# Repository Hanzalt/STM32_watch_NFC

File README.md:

# HolTyc Smartwatch

A smartwatch designed and engineered from scratch by Czech students. This is a hobby project intended to help others build their own PCB-based watches.

| Front | Back |
|:-----:|:----:|
|  |  |

---

## Features

- **Analog clock** — 12 addressable RGB LEDs (WS2812B) arranged in a clock ring
- **Digital clock** — HH:MM shown on a custom 7-segment display built using **Charlieplexing** (6 GPIO pins drive a 4-digit matrix with no external drivers)
- **Wrist-wake** — BMA400 accelerometer detects wrist raise, wakes the watch from sleep
- **Auto-brightness** — BH1750FVI ambient light sensor adjusts LED brightness automatically
- **6 color themes** — cycle through hour/minute color combinations
- **Time setting** — set time directly on the watch via buttons
- **Shooting mini-game** — hidden game accessible via simultaneous button press
- **Battery monitoring** — color-coded charging display
- **Ultra-low power** — STM32 STOP mode between interactions; RTC runs from LSE crystal

---

## Repository Structure

```
STM32_watch_NFC/
├── Firmware/               # STM32CubeIDE project (all firmware source code)
│   └── Core/
│       ├── Inc/            # Header files (main.h, BMA400.h, Din_LED.h, …)
│       └── Src/            # Source files (main.c, BMA400.c, Din_LED.c, …)
├── PCB/                    # KiCad project — schematic and PCB layout
│   └── STM32_watch_NFC/    # Main KiCad project files (.kicad_pcb, .kicad_sch, gerbers)
├── Firmware_old/           # Legacy firmware from earlier revisions (deprecated)
├── Datasheets_components/  # Datasheets for key ICs (STM32, BMA400, TPS63802, …)
├── HW_design/              # Hardware design notes and segment layout diagrams
├── Fotos/                  # PCB renders and design visuals
└── README.md
```

---

## Hardware

| Component | Part | Notes |
|-----------|------|-------|
| MCU | STM32L031G6U6 | Cortex-M0+, 32KB Flash, 8KB RAM |
| RGB LEDs | 12× WS2812B | Driven via TIM2 PWM + DMA |
| Display | Charlieplex matrix | 6 pins → 4-digit 7-segment (no external drivers) |
| Accelerometer | BMA400 | Wrist-wake via orientation interrupt |
| Light sensor | BH1750FVI | Auto-brightness (I2C) |
| Power converter | TPS63802 | Buck-boost regulator |
| RTC crystal | 32.768 kHz LSE | Accurate timekeeping in sleep |
| Buzzer | Passive | ~2.7 kHz tone |

The HH:MM display is built entirely with Charlieplexing — 6 GPIO pins control a 4-digit 7-segment matrix with no shift registers or external display drivers.

### Power Schematic

> **Note:** The PCB had NFC hardware (ST25R3916B antenna area), but NFC functionality was scrapped during development. No NFC code exists in the firmware.

---

## Getting Started

### Requirements

- [STM32CubeIDE](https://www.st.com/en/development-tools/stm32cubeide.html) (recommended: 1.14+)
- ST-Link programmer (or compatible SWD debugger)
- The watch hardware (or a compatible STM32L031 dev board for partial testing)

### Import & Build

1. Open STM32CubeIDE.
2. Go to **File → Import → General → Existing Projects into Workspace**.
3. Set the root directory to `Firmware/` and select the project.
4. Click **Finish**.
5. Build with **Project → Build Project** (or `Ctrl+B`).

### Flash

1. Connect your ST-Link to the watch via the SWD pads on the PCB.
2. In STM32CubeIDE, go to **Run → Debug Configurations** and select the ST-Link configuration.
3. Click **Debug** (or **Run**) to flash and start.

Alternatively, flash the compiled `.elf` / `.bin` from `Firmware/Debug/` using **STM32CubeProgrammer**.

### First Boot

- The RTC starts paused at 00:00:00. Set the time via **Button_R long-press** → enter `changeTime` mode.
- Time resets on power loss (no backup registers).

---

## Button Reference

| Button | Short press | Long press (≥1 s) |
|--------|-------------|-------------------|
| Button_R | Show RGB analog clock | Enter time-set mode |
| Button_LT | Show digital clock | Enter charging display |
| Button_LB | Show digital clock | Cycle color theme |
| Button_R + Button_LB | Enter shooting game | — |

---

## PCB

KiCad source files are in `PCB/STM32_watch_NFC/`. Gerber files ready for manufacturing are in `PCB/STM32_watch_NFC/gerber/`. A panelized version is available in `PCB/Panelized_watch/`.

---

## License

MIT License

Copyright (c) 2025 HolTyc

Permission is hereby granted, free of charge, to any person obtaining a copy of this software and associated documentation files (the "Software"), to deal in the Software without restriction, including without limitation the rights to use, copy, modify, merge, publish, distribute, sublicense, and/or sell copies of the Software, and to permit persons to whom the Software is furnished to do so, subject to the following conditions:

The above copyright notice and this permission notice shall be included in all copies or substantial portions of the Software.

THE SOFTWARE IS PROVIDED "AS IS", WITHOUT WARRANTY OF ANY KIND, EXPRESS OR IMPLIED, INCLUDING BUT NOT LIMITED TO THE WARRANTIES OF MERCHANTABILITY, FITNESS FOR A PARTICULAR PURPOSE AND NONINFRINGEMENT. IN NO EVENT SHALL THE AUTHORS OR COPYRIGHT HOLDERS BE LIABLE FOR ANY CLAIM, DAMAGES OR OTHER LIABILITY, WHETHER IN AN ACTION OF CONTRACT, TORT OR OTHERWISE, ARISING FROM, OUT OF OR IN CONNECTION WITH THE SOFTWARE OR THE USE OR OTHER DEALINGS IN THE SOFTWARE.

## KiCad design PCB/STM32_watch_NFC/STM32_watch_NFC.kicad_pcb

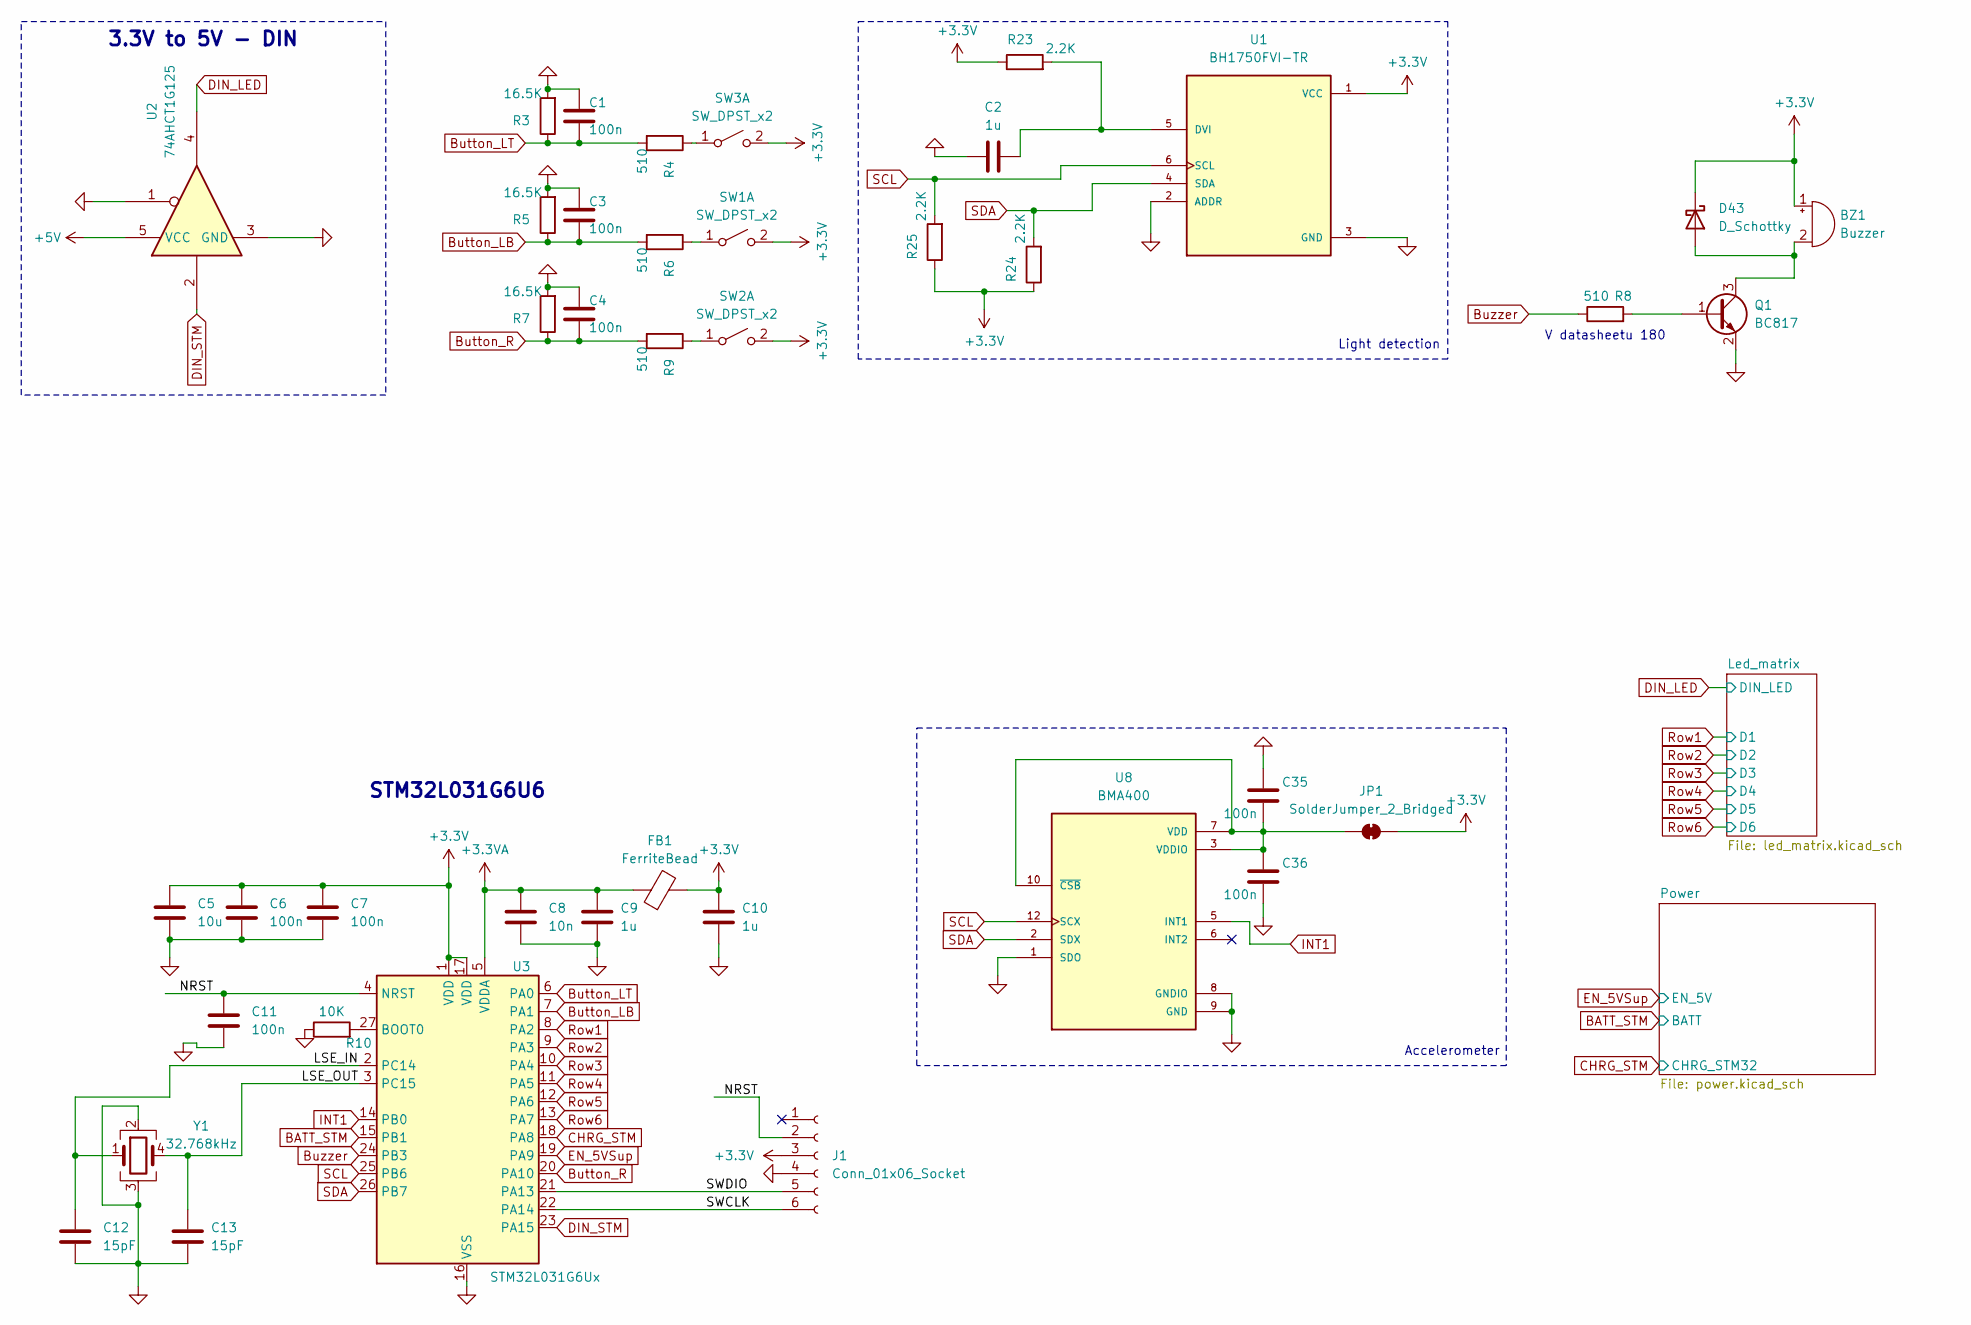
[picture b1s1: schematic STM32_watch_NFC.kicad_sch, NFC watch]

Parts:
BZ1: Buzzer; Buzzer_SMD; LCSC C95299
C1, C3, C4, C6, C7, C11, C35, C36: 100n; C_0201_0603Metric; LCSC C7393837
C2, C9, C10: 1u; C_0402_1005Metric; LCSC C52923
C5: 10u; C_0603_1608Metric; LCSC C19702
C8: 10n; C_0402_1005Metric; LCSC C15195
C12, C13: 15pF; C_0402_1005Metric; LCSC C1548
D43: D_Schottky; D_SOD-523; LCSC C727120
FB1: FerriteBead; L_0603_1608Metric; LCSC C1002
J1: Conn_01x06_Socket; JST_SUR_SM06B-SURS-TF_1x06-1MP_P0.80mm_Horizontal; LCSC C495545
JP1: SolderJumper_2_Bridged; SolderJumper-2_P1.3mm_Bridged_RoundedPad1.0x1.5mm
Q1: BC817; SOT-23; LCSC C52801
R3, R5, R7: 16.5K; R_0805_2012Metric; LCSC C104028
R4, R6, R8, R9: 510; R_0402_1005Metric; LCSC C25123
R10: 10K; R_0402_1005Metric; LCSC C25744
R23, R24, R25: 2.2K; R_0402_1005Metric; LCSC C25879
SW1, SW2, SW3: SW_DPST_x2; Panasonic_EVQPUJ_EVQPUA; LCSC C128539
U1: BH1750FVI-TR; XDCR_BH1750FVI-TR; LCSC C78960
U2: 74AHCT1G125; SOT-353_SC-70-5; LCSC C350557
U3: STM32L031G6Ux; QFN-28_4x4mm_P0.5mm; LCSC C96514
U8: BMA400; XDCR_BMA400
Y1: 32.768kHz; Crystal_SMD_SeikoEpson_MC146-4Pin_6.7x1.5mm; LCSC C7466130

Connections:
+3.3V: BZ1.1 (+), C5.1, C6.1, C7.1, C10.2, D43.1 (K), FB1.2, J1.3, JP1.2 (B), R23.1, R24.1, R25.1, SW1.2 (B), SW2.2 (B), SW3.2 (B), U1.1 (VCC), U3.1 (VDD), U3.17 (VDD); also elsewhere on the board
+3.3VA: C8.1, C9.2, FB1.1, U3.5 (VDDA)
+5V: U2.5 (VCC); also elsewhere on the board
/LSE_IN: C12.1, U3.2 (PC14), Y1.1
/LSE_OUT: C13.1, U3.3 (PC15), Y1.4
/NRST: C11.1, J1.2, U3.4 (NRST)
/SWCLK: J1.6, U3.22 (PA14)
/SWDIO: J1.5, U3.21 (PA13)
BATT_STM: U3.15 (PB1); also elsewhere on the board
Button_LB: C3.2, R5.1, R6.2, U3.7 (PA1)
Button_LT: C1.2, R3.1, R4.2, U3.6 (PA0)
Button_R: C4.2, R7.1, R9.2, U3.20 (PA10)
Buzzer: R8.1, U3.24 (PB3)
CHRG_STM: U3.18 (PA8); also elsewhere on the board
DIN_LED: U2.4; also elsewhere on the board
DIN_STM: U2.2, U3.23 (PA15)
EN_5VSup: U3.19 (PA9); also elsewhere on the board
GND: C1.1, C2.2, C3.1, C4.1, C5.2, C6.2, C7.2, C8.2, C9.1, C10.1, C11.2, C12.2, C13.2, C35.1, C36.2, J1.4, Q1.2 (E), R3.2, R5.2, R7.2, R10.1, U1.2 (ADDR), U1.3 (GND), U2.1, U2.3 (GND), U3.16 (VSS), U3.28 (VSS), U8.1 (SDO), U8.8 (GNDIO), U8.9 (GND), Y1.2, Y1.3; also elsewhere on the board
INT1: U3.14 (PB0), U8.5 (INT1)
unnamed: BZ1.2 (-), D43.2 (A), Q1.3 (C)
unnamed: C35.2, C36.1, JP1.1 (A), U8.3 (VDDIO), U8.7 (VDD), U8.10 (~CSB)
unnamed: Q1.1 (B), R8.2
unnamed: R6.1, SW1.1 (A)
unnamed: R9.1, SW2.1 (A)
unnamed: R4.1, SW3.1 (A)
unnamed: C2.1, R23.2, U1.5 (DVI)
unnamed: R10.2, U3.27 (BOOT0)
Row1: U3.8 (PA2); also elsewhere on the board
Row2: U3.9 (PA3); also elsewhere on the board
Row3: U3.10 (PA4); also elsewhere on the board
Row4: U3.11 (PA5); also elsewhere on the board
Row5: U3.12 (PA6); also elsewhere on the board
Row6: U3.13 (PA7); also elsewhere on the board
SCL: R25.2, U1.6 (SCL), U3.25 (PB6), U8.12 (SCX)
SDA: R24.2, U1.4 (SDA), U3.26 (PB7), U8.2 (SDX)

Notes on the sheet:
Light detection
V datasheetu 180
Accelerometer
3.3V to 5V - DIN
STM32L031G6U6

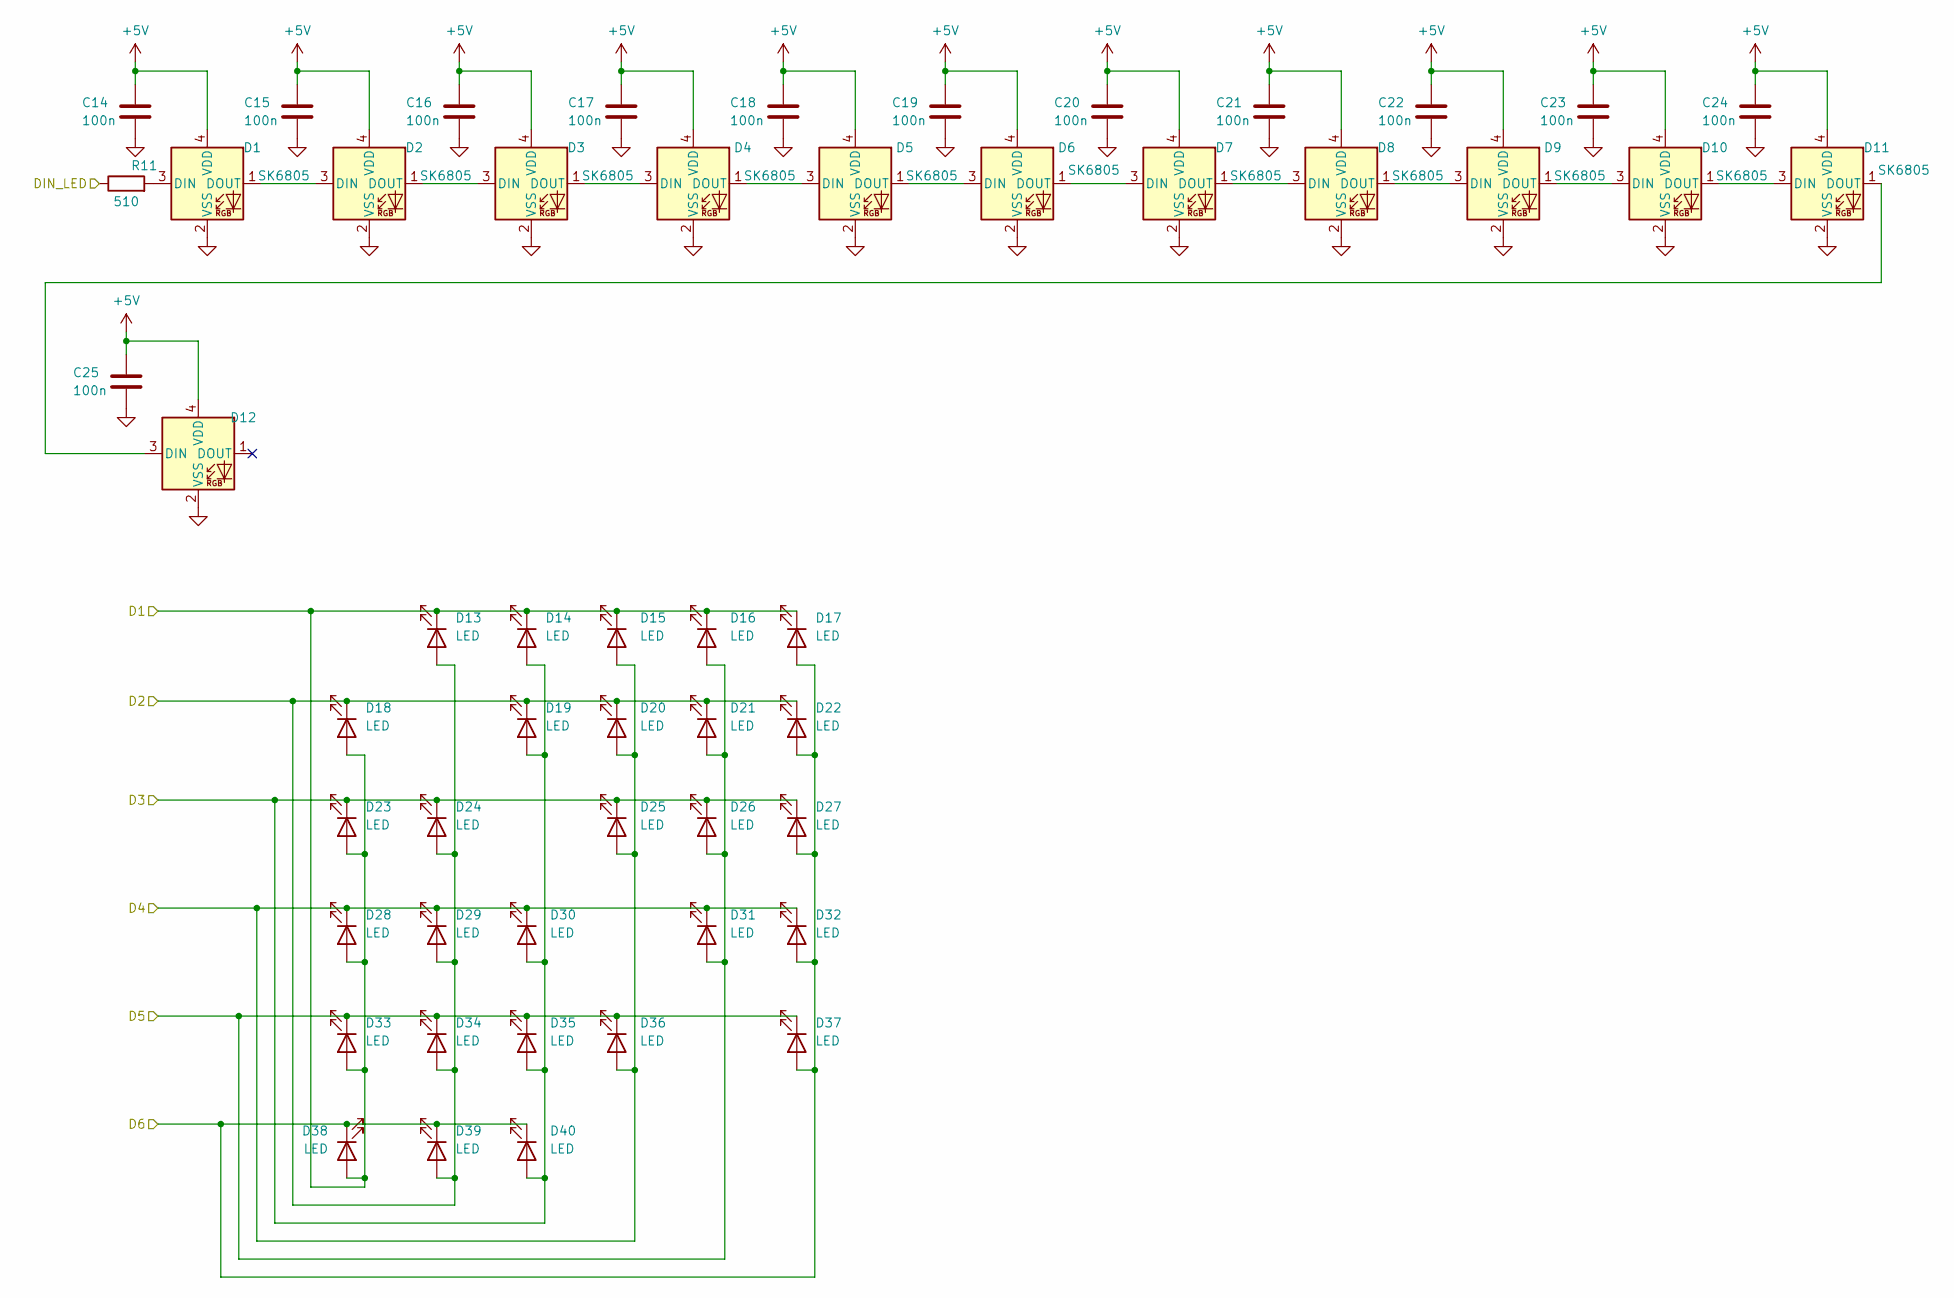
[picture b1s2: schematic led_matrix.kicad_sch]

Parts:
C14, C15, C16, C17, C18, C19, C20, C21, C22, C23, C24, C25: 100n; C_0201_0603Metric; LCSC C7393837
D1, D2, D3, D4, D5, D6, D7, D8, D9, D10, D11, D12: SK6805; LED_SK6812_EC15_1.5x1.5mm; LCSC C2890035
D13, D14, D15, D16, D17, D18, D19, D20, D21, D22, D23, D24, D25, D26, D27, D28, D29, D30, D31, D32, D33, D34, D35, D36, D37, D38, D39, D40: LED; LED_0402_1005Metric; LCSC C20613596
R11: 510; R_0402_1005Metric; LCSC C25123

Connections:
+5V: C14.1, C15.1, C16.1, C17.1, C18.1, C19.1, C20.1, C21.1, C22.1, C23.1, C24.1, C25.1, D1.4 (VDD), D2.4 (VDD), D3.4 (VDD), D4.4 (VDD), D5.4 (VDD), D6.4 (VDD), D7.4 (VDD), D8.4 (VDD), D9.4 (VDD), D10.4 (VDD), D11.4 (VDD), D12.4 (VDD); also elsewhere on the board
DIN_LED: R11.1; also elsewhere on the board
GND: C14.2, C15.2, C16.2, C17.2, C18.2, C19.2, C20.2, C21.2, C22.2, C23.2, C24.2, C25.2, D1.2 (VSS), D2.2 (VSS), D3.2 (VSS), D4.2 (VSS), D5.2 (VSS), D6.2 (VSS), D7.2 (VSS), D8.2 (VSS), D9.2 (VSS), D10.2 (VSS), D11.2 (VSS), D12.2 (VSS); also elsewhere on the board
unnamed: D1.3 (DIN), R11.2
unnamed: D1.1 (DOUT), D2.3 (DIN)
unnamed: D2.1 (DOUT), D3.3 (DIN)
unnamed: D3.1 (DOUT), D4.3 (DIN)
unnamed: D4.1 (DOUT), D5.3 (DIN)
unnamed: D5.1 (DOUT), D6.3 (DIN)
unnamed: D6.1 (DOUT), D7.3 (DIN)
unnamed: D7.1 (DOUT), D8.3 (DIN)
unnamed: D8.1 (DOUT), D9.3 (DIN)
unnamed: D9.1 (DOUT), D10.3 (DIN)
unnamed: D10.1 (DOUT), D11.3 (DIN)
unnamed: D11.1 (DOUT), D12.3 (DIN)
Row1: D13.1 (K), D14.1 (K), D15.1 (K), D16.1 (K), D17.1 (K), D18.2 (A), D23.2 (A), D28.2 (A), D33.2 (A), D38.2 (A); also elsewhere on the board
Row2: D13.2 (A), D18.1 (K), D19.1 (K), D20.1 (K), D21.1 (K), D22.1 (K), D24.2 (A), D29.2 (A), D34.2 (A), D39.2 (A); also elsewhere on the board
Row3: D14.2 (A), D19.2 (A), D23.1 (K), D24.1 (K), D25.1 (K), D26.1 (K), D27.1 (K), D30.2 (A), D35.2 (A), D40.2 (A); also elsewhere on the board
Row4: D15.2 (A), D20.2 (A), D25.2 (A), D28.1 (K), D29.1 (K), D30.1 (K), D31.1 (K), D32.1 (K), D36.2 (A); also elsewhere on the board
Row5: D16.2 (A), D21.2 (A), D26.2 (A), D31.2 (A), D33.1 (K), D34.1 (K), D35.1 (K), D36.1 (K), D37.1 (K); also elsewhere on the board
Row6: D17.2 (A), D22.2 (A), D27.2 (A), D32.2 (A), D37.2 (A), D38.1 (K), D39.1 (K), D40.1 (K); also elsewhere on the board

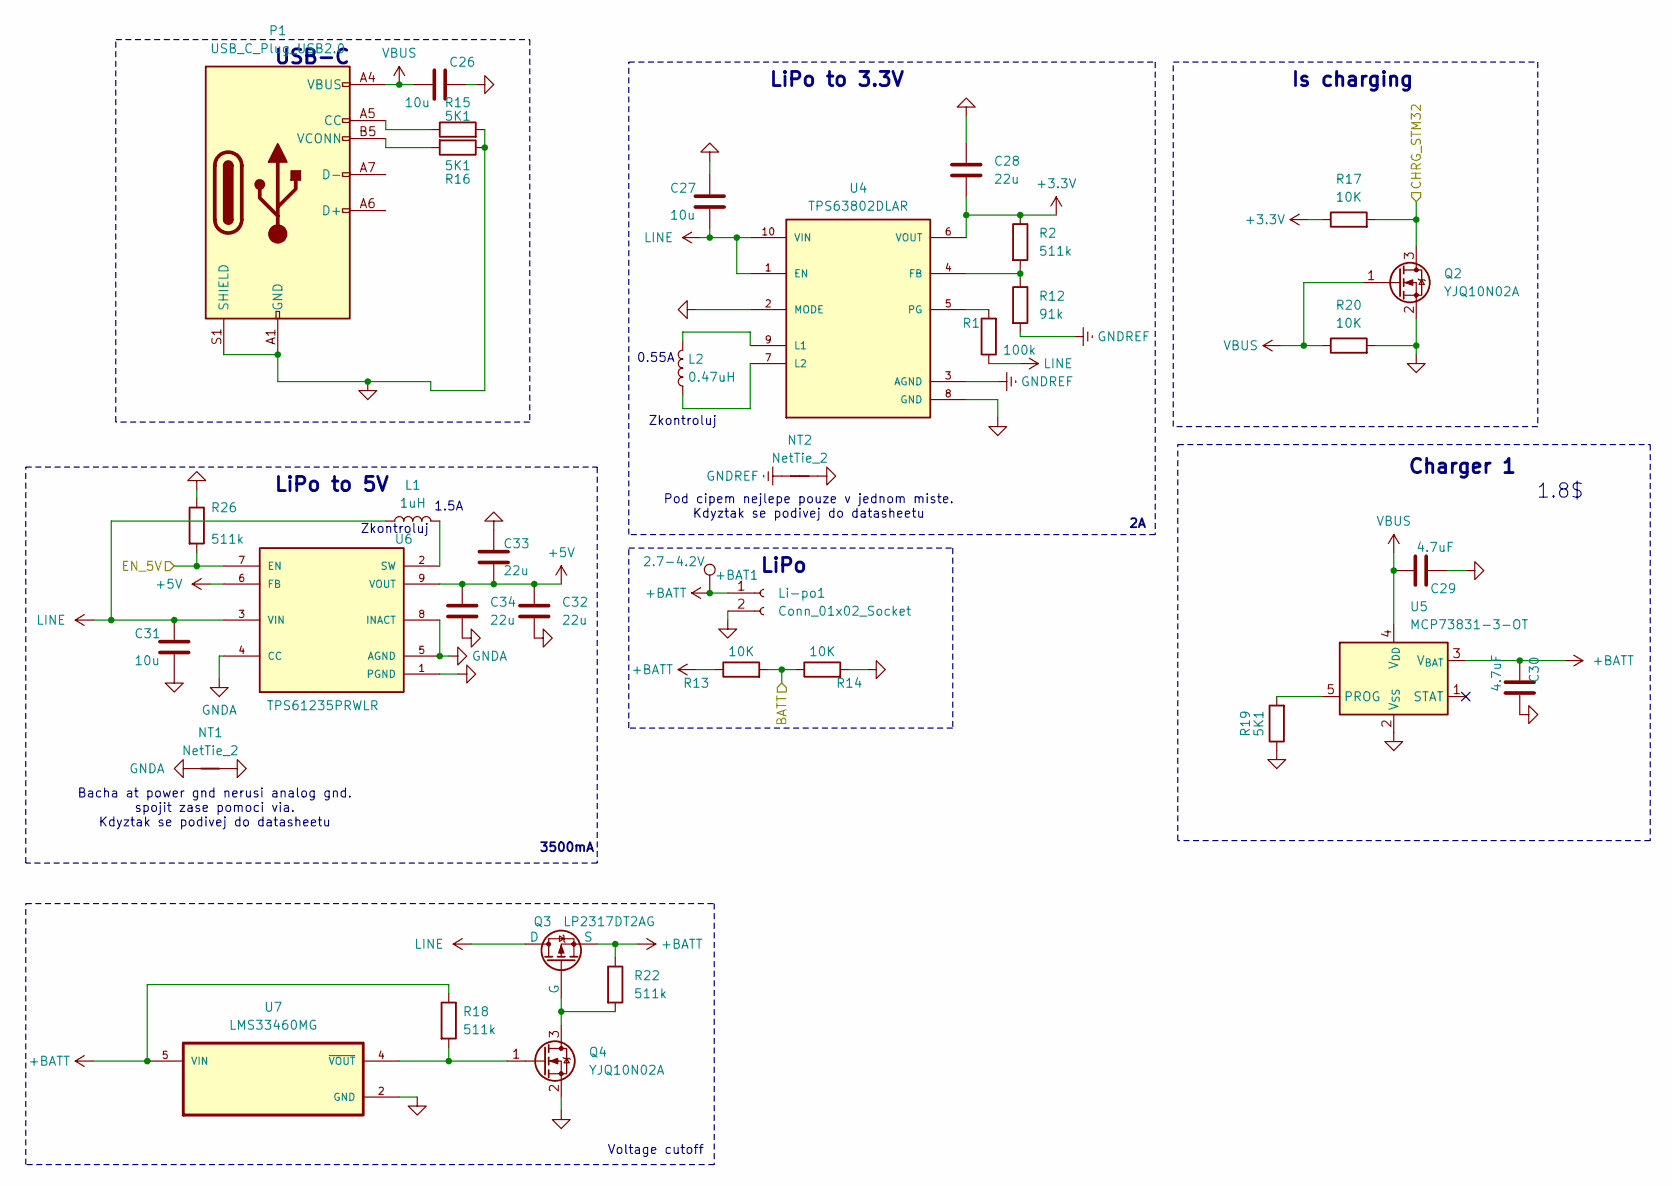
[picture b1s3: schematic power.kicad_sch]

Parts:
+BAT1: 2.7-4.2V; TestPoint_Pad_D1.5mm
C26, C27, C31: 10u; C_0603_1608Metric; LCSC C19702
C28, C32, C33, C34: 22u; C_0603_1608Metric; LCSC C59461
C29, C30: 4.7uF; C_0603_1608Metric; LCSC C19666
L1: 1uH; L_1008_2520Metric; LCSC C76795
L2: 0.47uH; L_0805_2012Metric; LCSC C370012
Li-po1: Conn_01x02_Socket; Molex_Pico-EZmate_78171-0002_1x02-1MP_P1.20mm_Vertical; LCSC C505023
NT1, NT2: NetTie_2; NetTie-2_SMD_Pad0.5mm
P1: USB_C_Plug_USB2.0; USB_C_Receptacle_GCT_USB4135-GF-A_6P_TopMnt_Horizontal; LCSC C2681548
Q2, Q4: YJQ10N02A; Diodes_UDFN2020-6_Type-F; LCSCv C919558
Q3: LP2317DT2AG; Diodes_UDFN2020-6_Type-F; LCSC C383254
R1: 100k; R_0603_1608Metric; LCSC C25803
R2, R18, R22, R26: 511k; R_0603_1608Metric; LCSC C2930114
R12: 91k; R_0603_1608Metric; LCSC C2907077
R13, R14, R17, R20: 10K; R_0402_1005Metric; LCSC C25744
R15, R16, R19: 5K1; R_0402_1005Metric; LCSC C25905
U4: TPS63802DLAR; VREG_TPS63802DLAR; LCSC C2845237
U5: MCP73831-3-OT; SOT-23-5; LCSC C625598
U6: TPS61235PRWLR; CONV_TPS61235PRWLR
U7: LMS33460MG; SOT65P210X110-5N; LCSC C95686

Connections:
+3.3V: C28.2, R2.1, R17.1, U4.6 (VOUT); also elsewhere on the board
+5V: C32.1, C33.2, C34.1, U6.6 (FB), U6.9 (VOUT); also elsewhere on the board
+BATT: +BAT1.1, C30.2, Li-po1.1, Q3.3 (S), R13.1, R18.1, R22.1, U5.3 (V_{BAT}), U7.5 (VIN)
/Power/DONE: U5.1 (STAT); also elsewhere on the board
BATT_STM: R13.2, R14.1; also elsewhere on the board
CHRG_STM: Q2.3 (D), R17.2; also elsewhere on the board
EN_5VSup: R26.2, U6.7 (EN); also elsewhere on the board
GND: C26.2, C27.1, C28.1, C29.2, C30.1, C31.2, C32.2, C33.1, C34.2, Li-po1.2, NT1.2, NT2.2, P1.A1 (GND), P1.A12 (GND), P1.B1 (GND), P1.B12 (GND), P1.S1 (SHIELD), Q2.2 (S), Q4.2 (S), R14.2, R15.2, R16.1, R19.1, R20.2, R26.1, U4.2 (MODE), U4.8 (GND), U5.2 (V_{SS}), U6.1 (PGND), U7.2 (GND), U7.3 (GND); also elsewhere on the board
GNDA: NT1.1, U6.4 (CC), U6.5 (AGND), U6.8 (INACT)
GNDREF: NT2.1, R12.2, U4.3 (AGND)
LINE: C27.2, C31.1, L1.1, Q3.1 (D), R1.1, U4.1 (EN), U4.10 (VIN), U6.3 (VIN)
unnamed: P1.A5 (CC), R15.1
unnamed: P1.B5 (VCONN), R16.2
unnamed: Q3.2 (G), Q4.3 (D), R22.2
unnamed: Q4.1 (G), R18.2, U7.4 (~VOUT)
unnamed: R2.2, R12.1, U4.4 (FB)
unnamed: L2.2, U4.9 (L1)
unnamed: L2.1, U4.7 (L2)
unnamed: R1.2, U4.5 (PG)
unnamed: R19.2, U5.5 (PROG)
unnamed: L1.2, U6.2 (SW)
VBUS: C26.1, C29.1, P1.A4 (VBUS), P1.A9 (VBUS), P1.B4 (VBUS), P1.B9 (VBUS), Q2.1 (G), R20.1, U5.4 (V_{DD}); also elsewhere on the board

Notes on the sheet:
Zkontroluj
Voltage cutoff
1.8$
LiPo to 3.3V
Bacha at power gnd nerusi analog gnd. spojit zase pomoci via. Kdyztak se podivej do datasheetu
Is charging
USB-C
3500mA
LiPo to 5V
0.55A
1.5A
LiPo
Charger 1
Pod cipem nejlepe pouze v jednom miste. Kdyztak se podivej do datasheetu

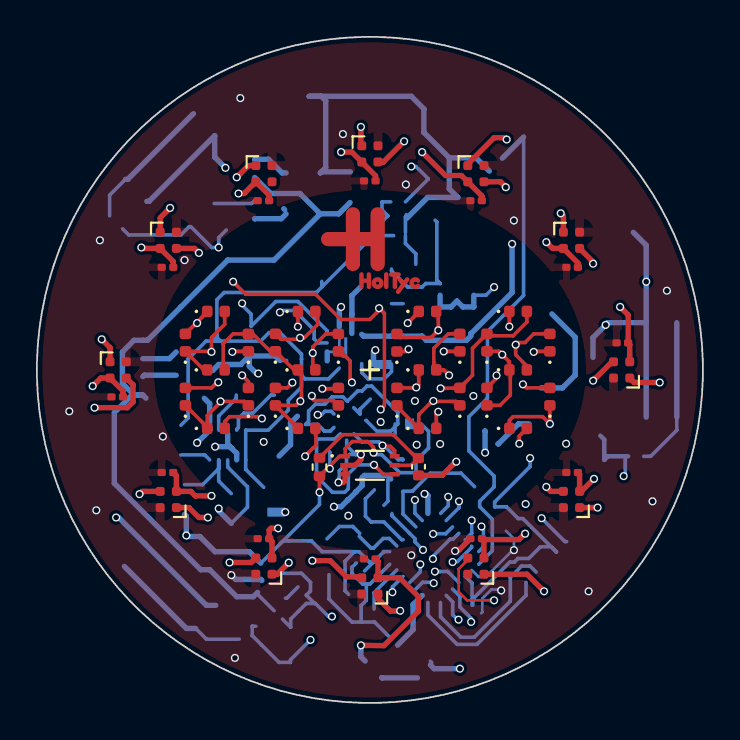
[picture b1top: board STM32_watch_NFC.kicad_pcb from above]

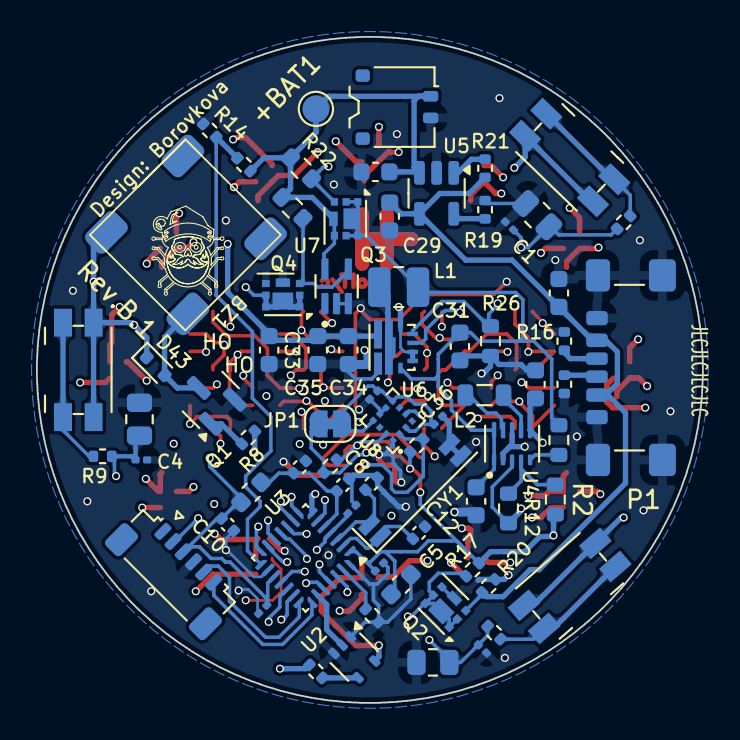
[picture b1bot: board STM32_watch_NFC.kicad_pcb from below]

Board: 4 copper layers, 37.0 x 37.0 mm, 130 parts (75 on the bottom side), 63 nets.

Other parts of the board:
R21: 10k; R_0402_1005Metric

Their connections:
/Power/DONE: R21.1; also elsewhere on the board
VBUS: R21.2; also elsewhere on the board

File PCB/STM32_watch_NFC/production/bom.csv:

Designator,Footprint,Quantity,Value,LCSC Part #
BZ1,Buzzer_SMD,1,Buzzer,C95299
"C1, C11, C14, C15, C16, C17, C18, C19, C20, C21, C22, C23, C24, C25, C3, C4, C6, C7",0201,18,100n,C7393837
"C10, C2, C27, C28, C9",0402,5,1u,C52923
"C12, C13",0402,2,15pF,C1548
"C26, C31, C32, C5",0603,4,10u,C19702
"C29, C30",0603,2,4.7uF,C19666
C8,0402,1,10n,C15195
"D1, D10, D11, D12, D2, D3, D4, D5, D6, D7, D8, D9",LED_SK6812_EC15_1.5x1.5mm,12,SK6805,C2890035
"D13, D14, D15, D16, D17, D18, D19, D20, D21, D22, D23, D24, D25, D26, D27, D28, D29, D30, D31, D32, D33, D34, D35, D36, D37, D38, D39, D40",0402,28,LED,C20613596
"D43, D45",D_SOD-523,2,D_Schottky,C727120
FB1,0603,1,FerriteBead,C1002
J1,JST_SUR_SM06B-SURS-TF_1x06-1MP_P0.80mm_Horizontal,1,Conn_01x06_Socket,C495545
J2,USB_C_Receptacle_GCT_USB4135-GF-A_6P_TopMnt_Horizontal,1,USB_C_Receptacle_PowerOnly_6P,C2927283
L1,L_Sunlord_SWPA3015S,1,22uH,C167761
LI-PO1,Molex_Pico-EZmate_78171-0002_1x02-1MP_P1.20mm_Vertical,1,Conn_01x02_Socket,C505023
Q1,SOT-23,1,BC817,C52801
Q2,SOT-23,1,AO3400A,
"R10, R13, R14, R17, R20, R21",0402,6,10K,C25744
"R11, R4, R6, R9",0402,4,510,C25123
"R15, R16, R19, R8",0402,4,5K1,C25905
"R18, R3, R5, R7",0805,4,16.5K,C104028
"R22, R23",0402,2,2.2K,C25879
"SW1, SW2, SW3",Panasonic_EVQPUJ_EVQPUA,3,SW_DPST_x2,C128539
U1,XDCR_BH1750FVI-TR,1,BH1750FVI-TR, C78960
U2,SOT-353_SC-70-5,1,74AHCT1G125,C151417
U3,QFN-28_4x4mm_P0.5mm,1,STM32L031G6Ux,C96514
U4,WSON-6-1EP_2x2mm_P0.65mm_EP1x1.6mm,1,LP5912-3.3DRV,C524780
U5,SOT-23-5,1,MCP73831-3-OT,C625598
U6,SOT-23-6,1,MT3608,C84817
Y1,Crystal_SMD_SeikoEpson_MC146-4Pin_6.7x1.5mm,1,32.768kHz,C7466130

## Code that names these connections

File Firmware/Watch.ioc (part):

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Mcu.Name=STM32L031G(4-6)Ux
Mcu.Package=UFQFPN28
Mcu.UserName=STM32L031G6Ux
PA1.GPIOParameters=GPIO_Label
PA1.GPIO_Label=Button_LB
PA1.Signal=GPXTI1
PA10.GPIOParameters=GPIO_Label
PA10.GPIO_Label=Button_R
PA10.Signal=GPXTI10
PA13.Mode=Serial_Wire
PA13.Signal=SYS_SWDIO
PA14.Mode=Serial_Wire
PA14.Signal=SYS_SWCLK
PA15.GPIOParameters=GPIO_Label
PA15.GPIO_Label=DIN_STM
PA15.Signal=S_TIM2_CH1
PA2.GPIOParameters=GPIO_Label
PA2.GPIO_Label=Row1
PA2.Signal=GPIO_Output
PA3.GPIOParameters=GPIO_Label
PA3.GPIO_Label=Row2
PA3.Signal=GPIO_Output
PA4.GPIOParameters=GPIO_Label
PA4.GPIO_Label=Row3
PA4.Signal=GPIO_Output
PA5.GPIOParameters=GPIO_Label
PA5.GPIO_Label=Row4
PA5.Signal=GPIO_Output
PA6.GPIOParameters=GPIO_Label
PA6.GPIO_Label=Row5
PA6.Signal=GPIO_Output
PA7.GPIOParameters=GPIO_Label
PA7.GPIO_Label=Row6
PA7.Signal=GPIO_Output
PA8.GPIOParameters=GPIO_Label,GPIO_ModeDefaultEXTI
PA8.GPIO_Label=Button_LT
PA8.GPIO_ModeDefaultEXTI=GPIO_MODE_IT_RISING_FALLING
PA8.Signal=GPXTI8
PA9.GPIOParameters=GPIO_Label
PA9.GPIO_Label=EN_5V
PA9.Signal=GPIO_Output
PB0.GPIOParameters=GPIO_Label
PB0.GPIO_Label=Accel
PB0.Signal=GPXTI0
PB1.GPIOParameters=GPIO_Label
PB1.GPIO_Label=BATT
PB1.Mode=IN9
PB1.Signal=ADC_IN9
PB3.GPIOParameters=GPIO_Speed,GPIO_PuPd,GPIO_Label,GPIO_ModeDefaultOutputPP
PB3.GPIO_Label=Buzzer
PB3.GPIO_ModeDefaultOutputPP=GPIO_MODE_OUTPUT_PP
PB3.GPIO_PuPd=GPIO_NOPULL
PB3.GPIO_Speed=GPIO_SPEED_FREQ_VERY_HIGH
PB3.Signal=GPIO_Output
PB6.GPIOParameters=GPIO_Pu
PB6.GPIO_Pu=GPIO_PULLUP
PB6.Mode=I2C
PB6.Signal=I2C1_SCL
PB7.GPIOParameters=GPIO_Pu
PB7.GPIO_Pu=GPIO_PULLUP
PB7.Mode=I2C
PB7.Signal=I2C1_SDA
PC14-OSC32_IN.Mode=LSE-External-Oscillator
PC14-OSC32_IN.Signal=RCC_OSC32_IN
PC15-OSC32_OUT.Mode=LSE-External-Oscillator
PC15-OSC32_OUT.Signal=RCC_OSC32_OUT
RCC.HSE_VALUE=8000000
RCC.SYSCLKFreq_VALUE=32000000
RCC.SYSCLKSource=RCC_SYSCLKSOURCE_PLLCLK
board=custom

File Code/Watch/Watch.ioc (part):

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Mcu.Name=STM32L031G(4-6)Ux
Mcu.Package=UFQFPN28
Mcu.UserName=STM32L031G6Ux
PA0-CK_IN.GPIOParameters=GPIO_Label
PA0-CK_IN.GPIO_Label=Button_LT
PA0-CK_IN.Signal=GPXTI0
PA1.GPIOParameters=GPIO_Label
PA1.GPIO_Label=Button_LB
PA1.Signal=GPXTI1
PA10.GPIOParameters=GPIO_Label
PA10.GPIO_Label=Button_R
PA10.Signal=GPXTI10
PA13.Mode=Serial_Wire
PA13.Signal=SYS_SWDIO
PA14.Mode=Serial_Wire
PA14.Signal=SYS_SWCLK
PA15.GPIOParameters=GPIO_Label
PA15.GPIO_Label=DIN
PA15.Signal=S_TIM2_CH1
PA3.GPIOParameters=GPIO_Label
PA3.GPIO_Label=SPI1_IRQ
PA3.Signal=GPXTI3
PA4.Mode=NSS_Signal_Hard_Output
PA4.Signal=SPI1_NSS
PA5.Mode=Full_Duplex_Master
PA5.Signal=SPI1_SCK
PA6.Mode=Full_Duplex_Master
PA6.Signal=SPI1_MISO
PA7.Mode=Full_Duplex_Master
PA7.Signal=SPI1_MOSI
PA8.GPIOParameters=GPIO_Label
PA8.GPIO_Label=CHRG
PA8.Signal=GPIO_Input
PA9.GPIOParameters=GPIO_Label
PA9.GPIO_Label=DONE
PA9.Signal=GPIO_Input
PB1.GPIOParameters=GPIO_Label
PB1.GPIO_Label=BATT
PB1.Mode=IN9
PB1.Signal=ADC_IN9
PC14-OSC32_IN.Mode=LSE-External-Oscillator
PC14-OSC32_IN.Signal=RCC_OSC32_IN
PC15-OSC32_OUT.Mode=LSE-External-Oscillator
PC15-OSC32_OUT.Signal=RCC_OSC32_OUT
RCC.HSE_VALUE=8000000
RCC.SYSCLKFreq_VALUE=32000000
RCC.SYSCLKSource=RCC_SYSCLKSOURCE_PLLCLK
board=custom

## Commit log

2024-03-23 README, PCB - test edit
2024-03-23 Update README.md - test
2024-03-23 STM32 first code
2024-03-24 Kicad - level shifter, LED, PCB layout. STM32 - PWM pin for LED
2024-03-24 Kicad - STM32 HW things, STM32 - Pin configuration
2024-03-24 KiCad - new LEDs, STM32
2024-03-28 Minor changes
2024-03-28 new version 1.13.0 -> 1.15.0 (STM32CubeIDE)
2024-03-28 Buttons test
2024-03-30 Kicad, Datasheets online
    Major update in PCB - new ST25R3916, LED array, bigger board, button
2024-04-03 Kicad
    Everything about power, started to make nfc - spiral antenna problem
2024-04-03 NFC antenna - Kicad
    I hope that antenna will work - I used TI coil designer, st25r - antenna tunning program and lots of datasheets/aplication notes
2024-04-06 Kicad - LCSC, footprints
    I managed to add all (I hope so :) ) LCSC values - which component will be used. With that I could determine all footprints
2024-04-07 Kicad - layout
    I placed all components in logical way. It is NOT routed.
2024-04-08 Kicad - Routing 1
    Starting routing. I did already a little bitte of routing
2024-04-08 Kicad - Routing 2
    TOP and BOT layers have rough routing, I routed on IN 1 layer all RGB LEDs - so on TOP will not be any traces
2024-04-10 Kicad - Routing 3
    Everything is routed BUT I found out I cant use blind/buried vias so... I need to redesign all vias :0
2024-04-12 Kicad - Routing 4
    Completed version. I just need to add graphics :)
2024-07-29 Coding LEDs
    Library for led management, buttons
2024-09-24 CODING #2 Working watch - time editing, showing time
2024-10-06 CODING #3 - Better timing with LEDs, improvements/bugs
2024-10-06 CODING #4 - function watch - it is FINALLY SHOWING TIME
2024-10-19 CODING #5 working Time and ADC for battery value
2024-12-30 LAST NFC
2025-01-04 URX watch #1
    pcb is NOT panelizated
2025-01-04 new branch
2025-01-04 NFC is back
2025-01-04 Kicad - new Routing 1
    Led matrix sheet added
2025-01-05 Kicad - new Routing 2
    4 7-segment RGB displays for time - pretty crazy I would say
2025-01-18 Kicad - new Routing 3
    TM1637 7-segment driver
2025-01-18 Kicad - new Routing 3.5
    Nothing special
2025-01-19 Kicad - new Routing 4.5
    NEW 7-segment display + connection, new charger, charging status
2025-01-21 Kicad/STM - new Routing 5
    All STM32 peripherals connected, new firmware file + new code in it :)
2025-01-26 TM1637 - in next commit I will delete the driver and connect the leds directly through matrix
2025-01-28 Kicad/STM - new Routing 6
    Version before Boston to work on it there - needs to replace every component :(
2025-04-26 REBORN - new design lead
    We have new vision for watches future so we will see
2025-06-18 Component placement
    I placed every component in logical way
2025-06-25 Routing #1
    Starting routing
2025-06-25 Routing #2
    Almost completed, only small touches and Design look :)
2025-06-28 Routing #3
    Done with routing - meet with DennyBrambor and teaching him how to route :)
2025-06-29 Routing #4
    Unfortunately I had to change all vias to be 0.45/0.3 so it was a lot of pain :)
2025-07-10 Revision.B.0
    Production folder in panelized_watch was send to production. YAAAH
2025-08-05 Programming rev.B.0
    Lots of changes and lots of stuff works now :)
2025-10-03 Programming rev.B.0 #1
    New functions - battery. Time works now
2025-10-03 Programming rev.B.0 #2
    Color change mode. 24H standart and changed from 06 - 6
2025-11-02 Last HW version before rework
2025-11-24 Whole power schema
    I draw the whole power section and I am starting to create accelerometer with gyro
2025-11-26 Schema done
    I redraw some footprints and added accelerometer with gyro
2025-12-01 PCB rev.B.1 #1
    it is pretty hard to use the same placement
2025-12-02 PCB rev.B.1 #2
    every component has logical placement
2025-12-02 PCB rev.B.1 #3
    routing almost done - now checking and silkscreen
2025-12-07 REV.B.1 before manufacturing
2025-12-07 Panelize rev.B.1
2025-12-15 rev.B.1
2026-01-09 Programming rev.B.1 #1
    quality of life changes and bug fixes
2026-03-17 Programming
    working battery, color change + lot of other stuff
2026-03-28 GAME and README
2026-03-28 README.md edit #1
    Picture changes
2026-03-28 Update README.md #2
2026-03-28 Update README.md #3
